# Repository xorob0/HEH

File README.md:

Ce repo contient une partie de mes projets et cours concernant mon cursus à la 
HEH.
Ils sont dipsonible sous la license Attribution 4.0 International (CC BY 4.0)

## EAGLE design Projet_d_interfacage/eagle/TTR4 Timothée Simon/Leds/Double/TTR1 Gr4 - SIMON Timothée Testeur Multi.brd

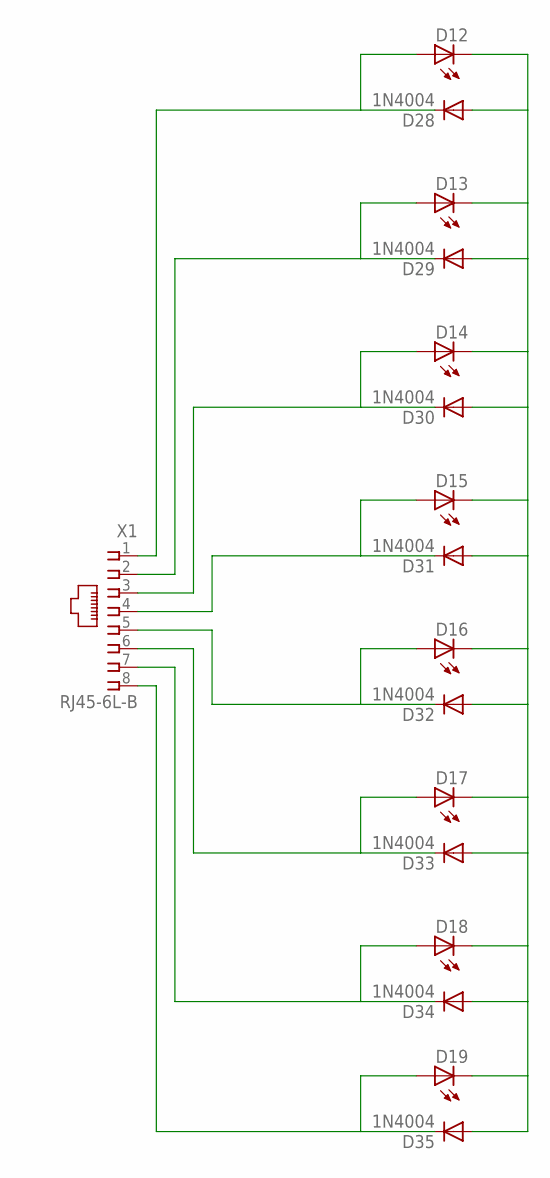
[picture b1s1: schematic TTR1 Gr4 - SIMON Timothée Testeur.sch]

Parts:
D12, D13, D14, D15, D16, D17, D18, D19: LED5MM
D28, D29, D30, D31, D32, D33, D34, D35: 1N4004; DO41-10
X1: RJ45-6L-B; RJ45-NO-SHIELD

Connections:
unnamed: D12.K (C), D13.K (C), D14.K (C), D15.K (C), D16.K (C), D17.K (C), D18.K (C), D19.K (C), D28.A, D29.A, D30.A, D31.A, D32.A, D33.A, D34.A, D35.A
unnamed: D12.A, D28.C, X1.1
unnamed: D13.A, D29.C, X1.2
unnamed: D14.A, D30.C, X1.3
unnamed: D15.A, D31.C, X1.4
unnamed: D16.A, D32.C, X1.5
unnamed: D17.A, D33.C, X1.6
unnamed: D18.A, D34.C, X1.7
unnamed: D19.A, D35.C, X1.8

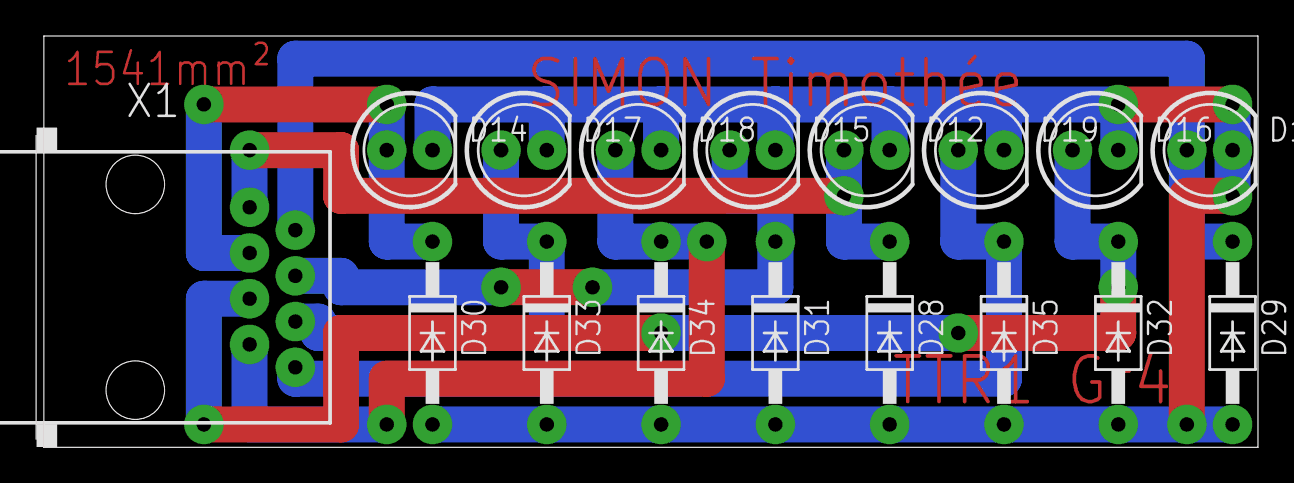
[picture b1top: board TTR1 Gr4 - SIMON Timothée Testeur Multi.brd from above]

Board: 2 copper layers, 67.9 x 22.8 mm, 17 parts (0 on the bottom side), 9 nets.

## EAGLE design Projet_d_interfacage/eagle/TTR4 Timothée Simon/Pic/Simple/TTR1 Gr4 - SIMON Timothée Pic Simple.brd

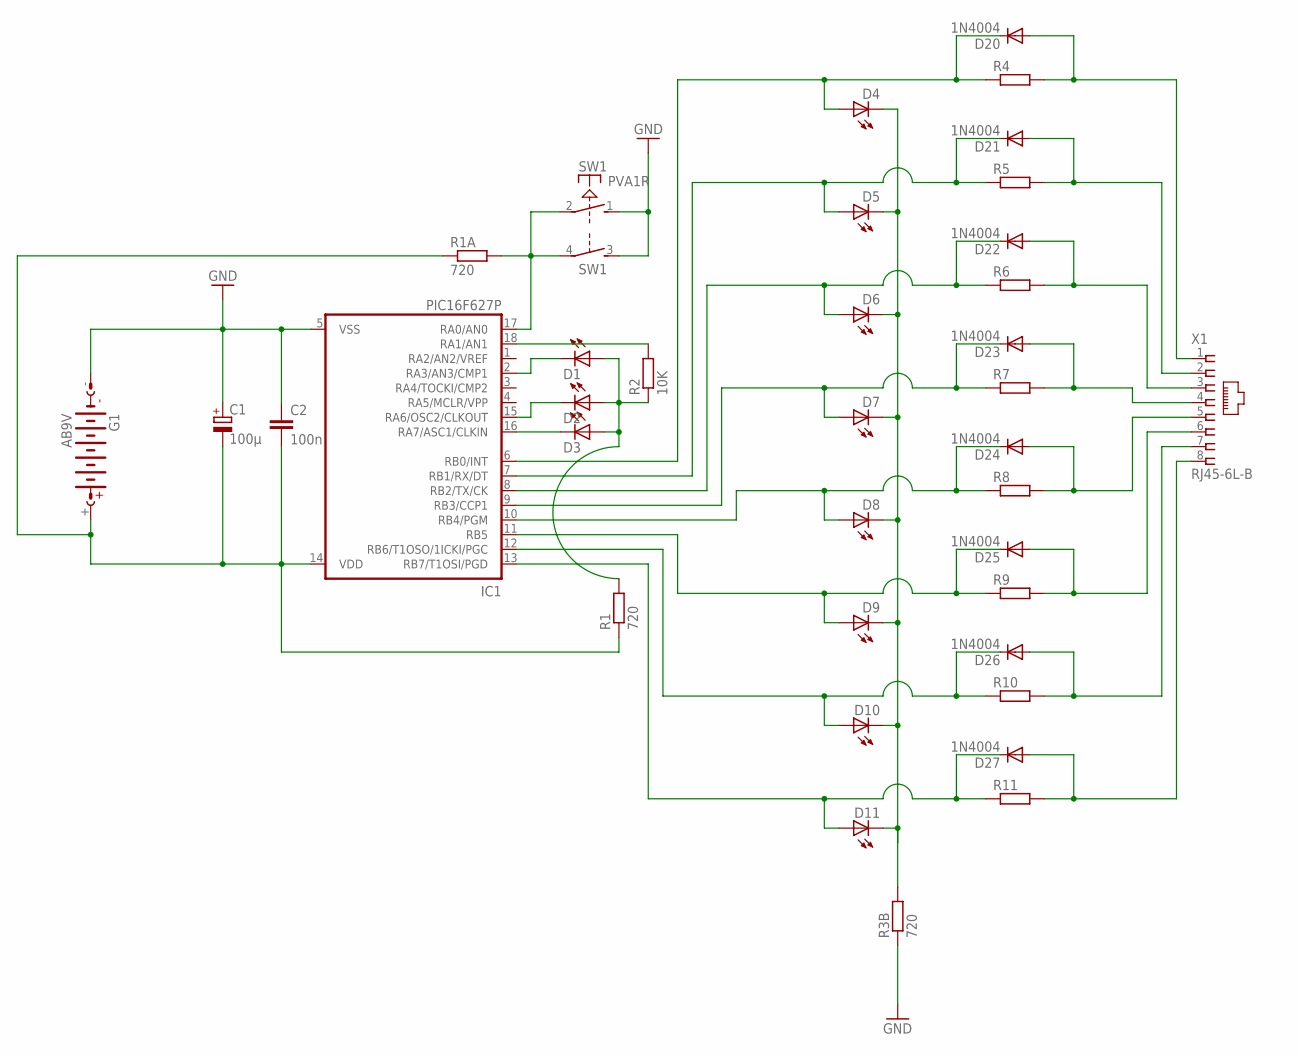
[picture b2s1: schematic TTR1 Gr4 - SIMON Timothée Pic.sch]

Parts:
C1: 100µ; E5-6
C2: 100n; C050-024X044
D1, D2, D3, D4, D5, D6, D7, D8, D9, D10, D11: LED5MM
D20, D21, D22, D23, D24, D25, D26, D27: 1N4004; DO41-10
G1: AB9V
IC1: PIC16F627P; DIL18
R1, R1A, R3B: 720; 0204/7
R2: 10K; 0204/7
R4, R5, R6, R7, R8, R9, R10, R11: R-EU_0204/7; 0204/7
SW1: PVA1R
X1: RJ45-6L-B; RJ45-NO-SHIELD

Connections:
D20: D4.A, D20.C, IC1.6 (RB0/INT), R4.1
GND: C1.+, C2.1, G1.-, IC1.5 (VSS), R3B.1, SW1.1 (S), SW1.3 (S)
unnamed: D5.A, D21.C, IC1.7 (RB1/RX/DT), R5.1
unnamed: D2.K (C), IC1.15 (RA6/OSC2/CLKOUT)
unnamed: IC1.18 (RA1/AN1), R2.2
unnamed: D7.A, D23.C, IC1.9 (RB3/CCP1), R7.1
unnamed: IC1.17 (RA0/AN0), R1A.2, SW1.2, SW1.4
unnamed: D1.A, D2.A, D3.A, R1.2, R2.1
unnamed: D21.A, R5.2, X1.2
unnamed: D1.K (C), IC1.2 (RA3/AN3/CMP1)
unnamed: D9.A, D25.C, IC1.11 (RB5), R9.1
unnamed: D3.K (C), IC1.16 (RA7/ASC1/CLKIN)
unnamed: D6.A, D22.C, IC1.8 (RB2/TX/CK), R6.1
unnamed: D23.A, R7.2, X1.4
unnamed: D20.A, R4.2, X1.1
unnamed: D8.A, D24.C, IC1.10 (RB4/PGM), R8.1
unnamed: D25.A, R9.2, X1.6
unnamed: D26.A, R10.2, X1.7
unnamed: D4.K (C), D5.K (C), D6.K (C), D7.K (C), D8.K (C), D9.K (C), D10.K (C), D11.K (C), R3B.2
unnamed: D24.A, R8.2, X1.5
unnamed: D27.A, R11.2, X1.8
unnamed: C1.-, C2.2, G1.+, IC1.14 (VDD), R1.1, R1A.1
unnamed: D10.A, D26.C, IC1.12 (RB6/T1OSO/1ICKI/PGC), R10.1
unnamed: D22.A, R6.2, X1.3
unnamed: D11.A, D27.C, IC1.13 (RB7/T1OSI/PGD), R11.1

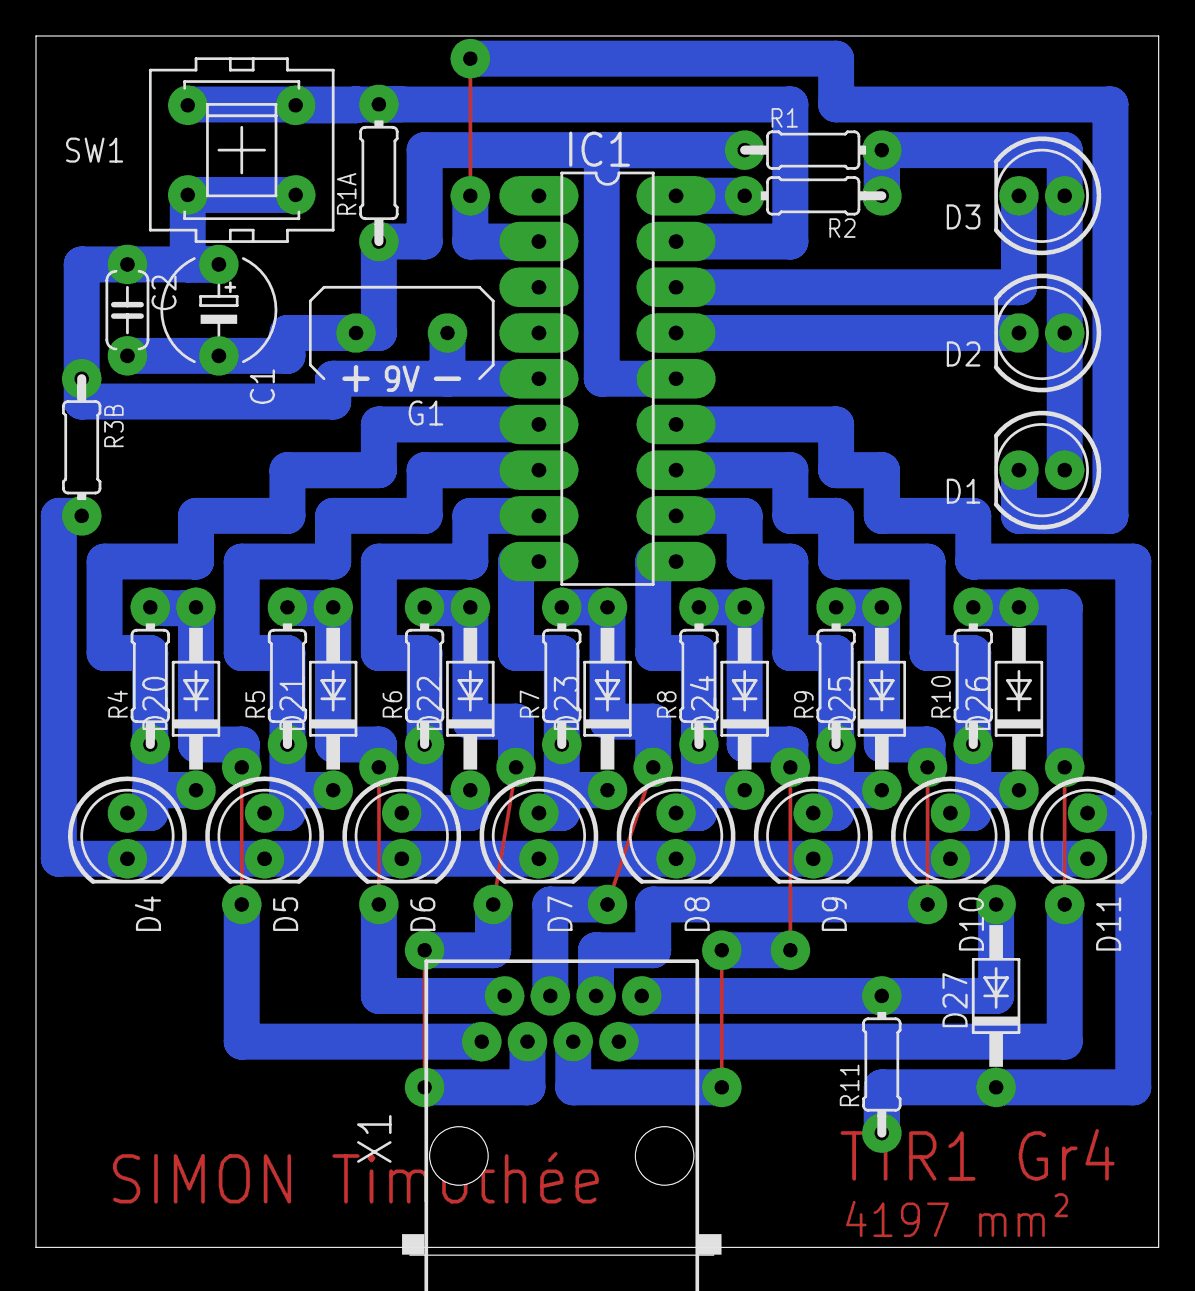
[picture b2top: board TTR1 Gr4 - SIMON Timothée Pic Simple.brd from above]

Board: 2 copper layers, 62.4 x 67.7 mm, 37 parts (0 on the bottom side), 25 nets.

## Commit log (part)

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2017-01-04 at 00:07:39/00:26:36 (28%)
2017-01-04 at 00:12:28/00:26:36 (46%)
2017-01-04 at 00:15:30/00:26:36 (58%)
2017-01-04 at 00:18:21/00:26:36 (68%)
2017-01-04 100%
2017-01-04 Correted some typos
2017-01-04 At 00:00:34/00:26:50 (2%)
2017-01-05 Corrected some typos and currently at 00:08:30/00:26:50 (31%) of Module2
2017-01-05 At 00:18:24/00:26:50 (68%)
2017-01-06 Finished the second module
2017-01-06 Corrected some typos
2017-01-06 Raw data from Dragon
2017-01-06 At 00:02:35/00:23:55 (10%)
2017-01-06 00:09:28/00:23:55 (39%)
2017-01-06 Corrected Typo
2017-01-06 Added a line in the README
2017-01-06 At 00:15:37/00:23:55 (65%)
2017-01-06 Finished Module 3
2017-01-06 Began module 4
2017-01-06 At 00:00:59/00:24:44 (4%)
2017-01-06 At 00:06:11/00:24:44 (25%)
2017-01-07 At 00:15:37/00:24:44 (63%)
2017-01-07 At 00:17:44/00:24:44 (71%)
2017-01-07 At 00:20:20/00:24:44 (82%)
2017-01-07 finished Module 4
2017-01-07 Raw text from Dragon
2017-01-14 Pages 86/144
2017-01-14 Page 103/144
2017-01-15 At 00:06:22/00:39:35 (16%)
2017-01-15 At 00:10:07/00:39:35 (25%)
2017-01-15 At 00:13:20/00:39:35 (33%)
2017-01-15 At 00:21:51/00:39:35 (55%)
2017-01-15 At 00:24:22/00:39:35 (61%)
2017-01-15 At 00:27:47/00:39:35 (70%)
2017-01-15 At 00:31:41/00:39:35 (80%)
2017-01-15 Finnished Module5
2017-01-15 Impoved layout
2017-01-15 corrected some errors
2017-01-15 Added title
2017-01-15 At 00:08:38/00:26:50 (32%)
2017-01-21 Nouveau résumé en électricité
2017-01-22 Finished first chapter
2017-01-22 Divided chapter to files
2017-01-22 Corrected file and generated PDF
2017-01-22 Page 10/70
2017-01-22 Modified README
2017-01-22 Page 15/70
2017-01-22 Page 27/70
2017-01-22 Page 39/70
2017-01-22 Page 43/70
2017-01-22 Page 49/70
2017-01-22 62/70
2017-01-22 Finished Chap2
2017-01-22 corrected indet
2017-01-24 corrected typos
2018-05-24 Ajout du code source du rapport d'arduino
2020-04-07 Adding new projet in monorepo
2020-04-07 updating new projects
2020-04-07 Adding new projects to monorepo
2020-04-07 Bump acorn from 5.7.3 to 5.7.4 in /Petclinic-Frontend
    Bumps [acorn](https://github.com/acornjs/acorn) from 5.7.3 to 5.7.4.
    - [Release notes](https://github.com/acornjs/acorn/releases)
    - [Commits](https://github.com/acornjs/acorn/compare/5.7.3...5.7.4)
2020-04-07 Bump mixin-deep from 1.3.1 to 1.3.2 in /Petclinic-Frontend
    Bumps [mixin-deep](https://github.com/jonschlinkert/mixin-deep) from 1.3.1 to 1.3.2.
    - [Release notes](https://github.com/jonschlinkert/mixin-deep/releases)
    - [Commits](https://github.com/jonschlinkert/mixin-deep/compare/1.3.1...1.3.2)
2020-04-07 Bump lodash.template from 4.4.0 to 4.5.0 in /Petclinic-Frontend
    Bumps [lodash.template](https://github.com/lodash/lodash) from 4.4.0 to 4.5.0.
    - [Release notes](https://github.com/lodash/lodash/releases)
    - [Commits](https://github.com/lodash/lodash/compare/4.4.0...4.5.0)
2020-04-07 Bump handlebars from 4.0.12 to 4.7.6 in /Petclinic-Frontend
    Bumps [handlebars](https://github.com/wycats/handlebars.js) from 4.0.12 to 4.7.6.
    - [Release notes](https://github.com/wycats/handlebars.js/releases)
    - [Changelog](https://github.com/wycats/handlebars.js/blob/master/release-notes.md)
    - [Commits](https://github.com/wycats/handlebars.js/compare/v4.0.12...v4.7.6)
2020-04-07 Bump eslint-utils from 1.3.1 to 1.4.3 in /Petclinic-Frontend
    Bumps [eslint-utils](https://github.com/mysticatea/eslint-utils) from 1.3.1 to 1.4.3.
    - [Release notes](https://github.com/mysticatea/eslint-utils/releases)
    - [Commits](https://github.com/mysticatea/eslint-utils/compare/v1.3.1...v1.4.3)
2020-04-07 Bump js-yaml from 3.12.0 to 3.13.1 in /Petclinic-Frontend
    Bumps [js-yaml](https://github.com/nodeca/js-yaml) from 3.12.0 to 3.13.1.
    - [Release notes](https://github.com/nodeca/js-yaml/releases)
    - [Changelog](https://github.com/nodeca/js-yaml/blob/master/CHANGELOG.md)
    - [Commits](https://github.com/nodeca/js-yaml/compare/3.12.0...3.13.1)
2020-06-08 Bump websocket-extensions from 0.1.3 to 0.1.4 in /Petclinic-Frontend
    Bumps [websocket-extensions](https://github.com/faye/websocket-extensions-node) from 0.1.3 to 0.1.4.
    - [Release notes](https://github.com/faye/websocket-extensions-node/releases)
    - [Changelog](https://github.com/faye/websocket-extensions-node/blob/master/CHANGELOG.md)
    - [Commits](https://github.com/faye/websocket-extensions-node/compare/0.1.3...0.1.4)
2020-08-01 Bump elliptic from 6.4.1 to 6.5.3 in /Petclinic-Frontend
    Bumps [elliptic](https://github.com/indutny/elliptic) from 6.4.1 to 6.5.3.
    - [Release notes](https://github.com/indutny/elliptic/releases)
    - [Commits](https://github.com/indutny/elliptic/compare/v6.4.1...v6.5.3)
2020-09-11 Bump http-proxy from 1.17.0 to 1.18.1 in /Petclinic-Frontend
    Bumps [http-proxy](https://github.com/http-party/node-http-proxy) from 1.17.0 to 1.18.1.
    - [Release notes](https://github.com/http-party/node-http-proxy/releases)
    - [Changelog](https://github.com/http-party/node-http-proxy/blob/master/CHANGELOG.md)
    - [Commits](https://github.com/http-party/node-http-proxy/compare/1.17.0...1.18.1)
2021-03-10 Bump elliptic from 6.4.1 to 6.5.4 in /Petclinic-Frontend
    Bumps [elliptic](https://github.com/indutny/elliptic) from 6.4.1 to 6.5.4.
    - [Release notes](https://github.com/indutny/elliptic/releases)
    - [Commits](https://github.com/indutny/elliptic/compare/v6.4.1...v6.5.4)
2021-03-31 Bump y18n from 3.2.1 to 3.2.2 in /Petclinic-Frontend
    Bumps [y18n](https://github.com/yargs/y18n) from 3.2.1 to 3.2.2.
    - [Release notes](https://github.com/yargs/y18n/releases)
    - [Changelog](https://github.com/yargs/y18n/blob/master/CHANGELOG.md)
    - [Commits](https://github.com/yargs/y18n/commits)
2021-05-07 Bump ua-parser-js from 0.7.19 to 0.7.28 in /Petclinic-Frontend
    Bumps [ua-parser-js](https://github.com/faisalman/ua-parser-js) from 0.7.19 to 0.7.28.
    - [Release notes](https://github.com/faisalman/ua-parser-js/releases)
    - [Commits](https://github.com/faisalman/ua-parser-js/compare/0.7.19...0.7.28)
2021-05-08 Bump handlebars from 4.7.6 to 4.7.7 in /Petclinic-Frontend
    Bumps [handlebars](https://github.com/wycats/handlebars.js) from 4.7.6 to 4.7.7.
    - [Release notes](https://github.com/wycats/handlebars.js/releases)
    - [Changelog](https://github.com/handlebars-lang/handlebars.js/blob/master/release-notes.md)
    - [Commits](https://github.com/wycats/handlebars.js/compare/v4.7.6...v4.7.7)
2021-05-09 Bump url-parse from 1.4.3 to 1.5.1 in /Petclinic-Frontend
    Bumps [url-parse](https://github.com/unshiftio/url-parse) from 1.4.3 to 1.5.1.
    - [Release notes](https://github.com/unshiftio/url-parse/releases)
    - [Commits](https://github.com/unshiftio/url-parse/compare/1.4.3...1.5.1)
2021-05-11 Bump hosted-git-info from 2.7.1 to 2.8.9 in /Petclinic-Frontend
    Bumps [hosted-git-info](https://github.com/npm/hosted-git-info) from 2.7.1 to 2.8.9.
    - [Release notes](https://github.com/npm/hosted-git-info/releases)
    - [Changelog](https://github.com/npm/hosted-git-info/blob/v2.8.9/CHANGELOG.md)
    - [Commits](https://github.com/npm/hosted-git-info/compare/v2.7.1...v2.8.9)
2021-05-28 Bump dns-packet from 1.3.1 to 1.3.4 in /Petclinic-Frontend
    Bumps [dns-packet](https://github.com/mafintosh/dns-packet) from 1.3.1 to 1.3.4.
    - [Release notes](https://github.com/mafintosh/dns-packet/releases)
    - [Changelog](https://github.com/mafintosh/dns-packet/blob/master/CHANGELOG.md)
    - [Commits](https://github.com/mafintosh/dns-packet/compare/v1.3.1...v1.3.4)
2021-06-08 Bump merge-deep from 3.0.2 to 3.0.3 in /Petclinic-Frontend
    Bumps [merge-deep](https://github.com/jonschlinkert/merge-deep) from 3.0.2 to 3.0.3.
    - [Release notes](https://github.com/jonschlinkert/merge-deep/releases)
    - [Commits](https://github.com/jonschlinkert/merge-deep/compare/3.0.2...3.0.3)
    ---
    updated-dependencies:
    - dependency-name: merge-deep
2021-08-04 Bump tar from 4.4.6 to 4.4.15 in /Petclinic-Frontend
    Bumps [tar](https://github.com/npm/node-tar) from 4.4.6 to 4.4.15.
    - [Release notes](https://github.com/npm/node-tar/releases)
    - [Changelog](https://github.com/npm/node-tar/blob/main/CHANGELOG.md)
    - [Commits](https://github.com/npm/node-tar/compare/v4.4.6...v4.4.15)
    ---
    updated-dependencies:
2021-08-12 Bump path-parse from 1.0.6 to 1.0.7 in /Petclinic-Frontend
    Bumps [path-parse](https://github.com/jbgutierrez/path-parse) from 1.0.6 to 1.0.7.
    - [Release notes](https://github.com/jbgutierrez/path-parse/releases)
    - [Commits](https://github.com/jbgutierrez/path-parse/commits/v1.0.7)
    ---
    updated-dependencies:
    - dependency-name: path-parse
2021-09-02 Bump tar from 4.4.6 to 4.4.19 in /Petclinic-Frontend
    Bumps [tar](https://github.com/npm/node-tar) from 4.4.6 to 4.4.19.
    - [Release notes](https://github.com/npm/node-tar/releases)
    - [Changelog](https://github.com/npm/node-tar/blob/main/CHANGELOG.md)
    - [Commits](https://github.com/npm/node-tar/compare/v4.4.6...v4.4.19)
    ---
    updated-dependencies:
2021-09-21 Bump tmpl from 1.0.4 to 1.0.5 in /Petclinic-Frontend
    Bumps [tmpl](https://github.com/daaku/nodejs-tmpl) from 1.0.4 to 1.0.5.
    - [Release notes](https://github.com/daaku/nodejs-tmpl/releases)
    - [Commits](https://github.com/daaku/nodejs-tmpl/commits/v1.0.5)
    ---
    updated-dependencies:
    - dependency-name: tmpl
2021-10-06 Bump url-parse from 1.4.3 to 1.5.3 in /Petclinic-Frontend
    Bumps [url-parse](https://github.com/unshiftio/url-parse) from 1.4.3 to 1.5.3.
    - [Release notes](https://github.com/unshiftio/url-parse/releases)
    - [Commits](https://github.com/unshiftio/url-parse/compare/1.4.3...1.5.3)
    ---
    updated-dependencies:
    - dependency-name: url-parse
2022-01-14 Bump follow-redirects from 1.5.9 to 1.14.7 in /Petclinic-Frontend
    Bumps [follow-redirects](https://github.com/follow-redirects/follow-redirects) from 1.5.9 to 1.14.7.
    - [Release notes](https://github.com/follow-redirects/follow-redirects/releases)
    - [Commits](https://github.com/follow-redirects/follow-redirects/compare/v1.5.9...v1.14.7)
    ---
    updated-dependencies:
    - dependency-name: follow-redirects
2022-02-19 Bump url-parse from 1.4.3 to 1.5.7 in /Petclinic-Frontend
    Bumps [url-parse](https://github.com/unshiftio/url-parse) from 1.4.3 to 1.5.7.
    - [Release notes](https://github.com/unshiftio/url-parse/releases)
    - [Commits](https://github.com/unshiftio/url-parse/compare/1.4.3...1.5.7)
    ---
    updated-dependencies:
    - dependency-name: url-parse
2022-02-27 Bump url-parse from 1.4.3 to 1.5.10 in /Petclinic-Frontend
    Bumps [url-parse](https://github.com/unshiftio/url-parse) from 1.4.3 to 1.5.10.
    - [Release notes](https://github.com/unshiftio/url-parse/releases)
    - [Commits](https://github.com/unshiftio/url-parse/compare/1.4.3...1.5.10)
    ---
    updated-dependencies:
    - dependency-name: url-parse
2022-10-06 Bump css-what from 2.1.2 to 2.1.3 in /Petclinic-Frontend
    Bumps [css-what](https://github.com/fb55/css-what) from 2.1.2 to 2.1.3.
    - [Release notes](https://github.com/fb55/css-what/releases)
    - [Commits](https://github.com/fb55/css-what/compare/v2.1.2...v2.1.3)
    ---
    updated-dependencies:
    - dependency-name: css-what
2022-12-05 Bump decode-uri-component from 0.2.0 to 0.2.2 in /Petclinic-Frontend
    Bumps [decode-uri-component](https://github.com/SamVerschueren/decode-uri-component) from 0.2.0 to 0.2.2.
    - [Release notes](https://github.com/SamVerschueren/decode-uri-component/releases)
    - [Commits](https://github.com/SamVerschueren/decode-uri-component/compare/v0.2.0...v0.2.2)
    ---
    updated-dependencies:
    - dependency-name: decode-uri-component
